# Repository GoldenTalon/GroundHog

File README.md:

# GroundHog
WPT inverter design with dynamic all off time and dynamic frequency.

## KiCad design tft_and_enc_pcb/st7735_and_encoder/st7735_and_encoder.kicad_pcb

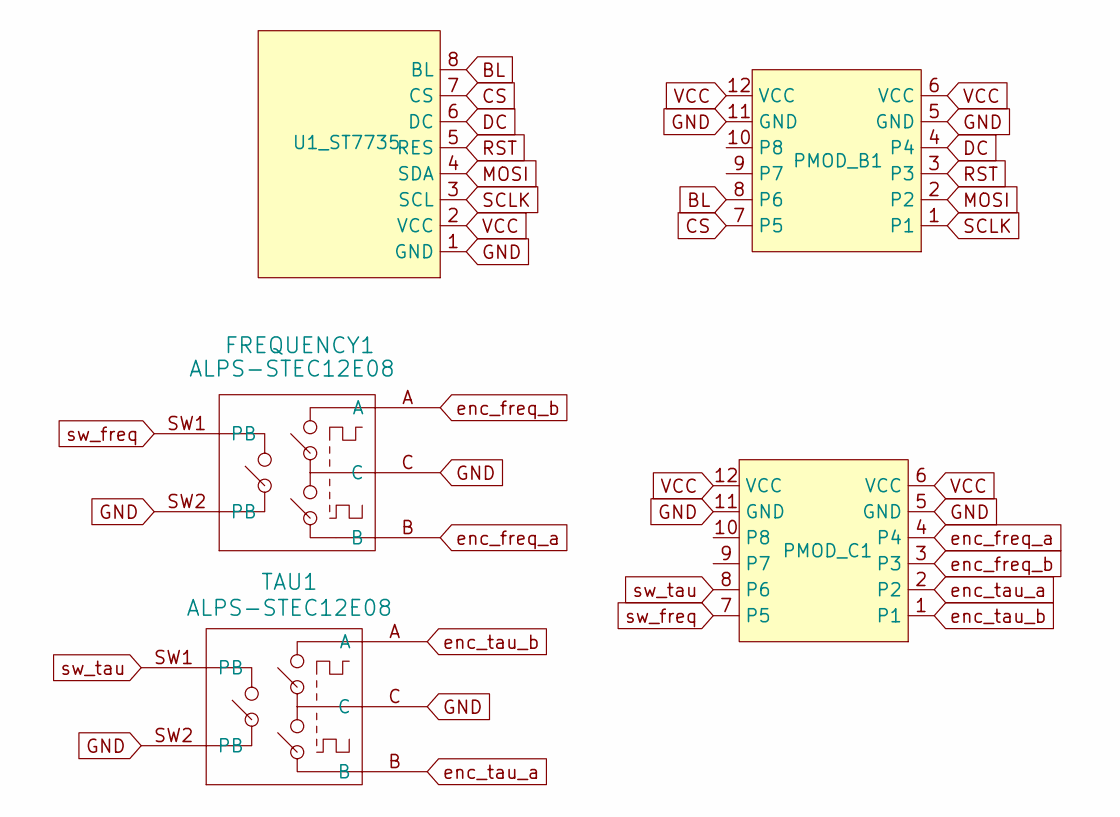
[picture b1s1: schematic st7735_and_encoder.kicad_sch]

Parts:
FREQUENCY1: ALPS-STEC12E08; ALPS_STEC12E08
PMOD_B1: pmod_end_launch
PMOD_C1: pmod_end_launch
TAU1: ALPS-STEC12E08; ALPS_STEC12E08
U1_ST7735: ST7735

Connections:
BL: PMOD_B1.8 (P6), U1_ST7735.8 (BL)
CS: PMOD_B1.7 (P5), U1_ST7735.7 (CS)
DC: PMOD_B1.4, U1_ST7735.6 (DC)
GND: FREQUENCY1.C, FREQUENCY1.SW2 (PB), PMOD_B1.5 (GND), PMOD_B1.11 (GND), PMOD_C1.5 (GND), PMOD_C1.11 (GND), TAU1.C, TAU1.SW2 (PB), U1_ST7735.1 (GND)
MOSI: PMOD_B1.2, U1_ST7735.4 (SDA)
RST: PMOD_B1.3, U1_ST7735.5 (RES)
SCLK: PMOD_B1.1, U1_ST7735.3 (SCL)
VCC: PMOD_B1.6 (VCC), PMOD_B1.12 (VCC), PMOD_C1.6 (VCC), PMOD_C1.12 (VCC), U1_ST7735.2 (VCC)
enc_freq_a: FREQUENCY1.B, PMOD_C1.4
enc_freq_b: FREQUENCY1.A, PMOD_C1.3
enc_tau_a: PMOD_C1.2, TAU1.B
enc_tau_b: PMOD_C1.1, TAU1.A
sw_freq: FREQUENCY1.SW1 (PB), PMOD_C1.7 (P5)
sw_tau: PMOD_C1.8 (P6), TAU1.SW1 (PB)

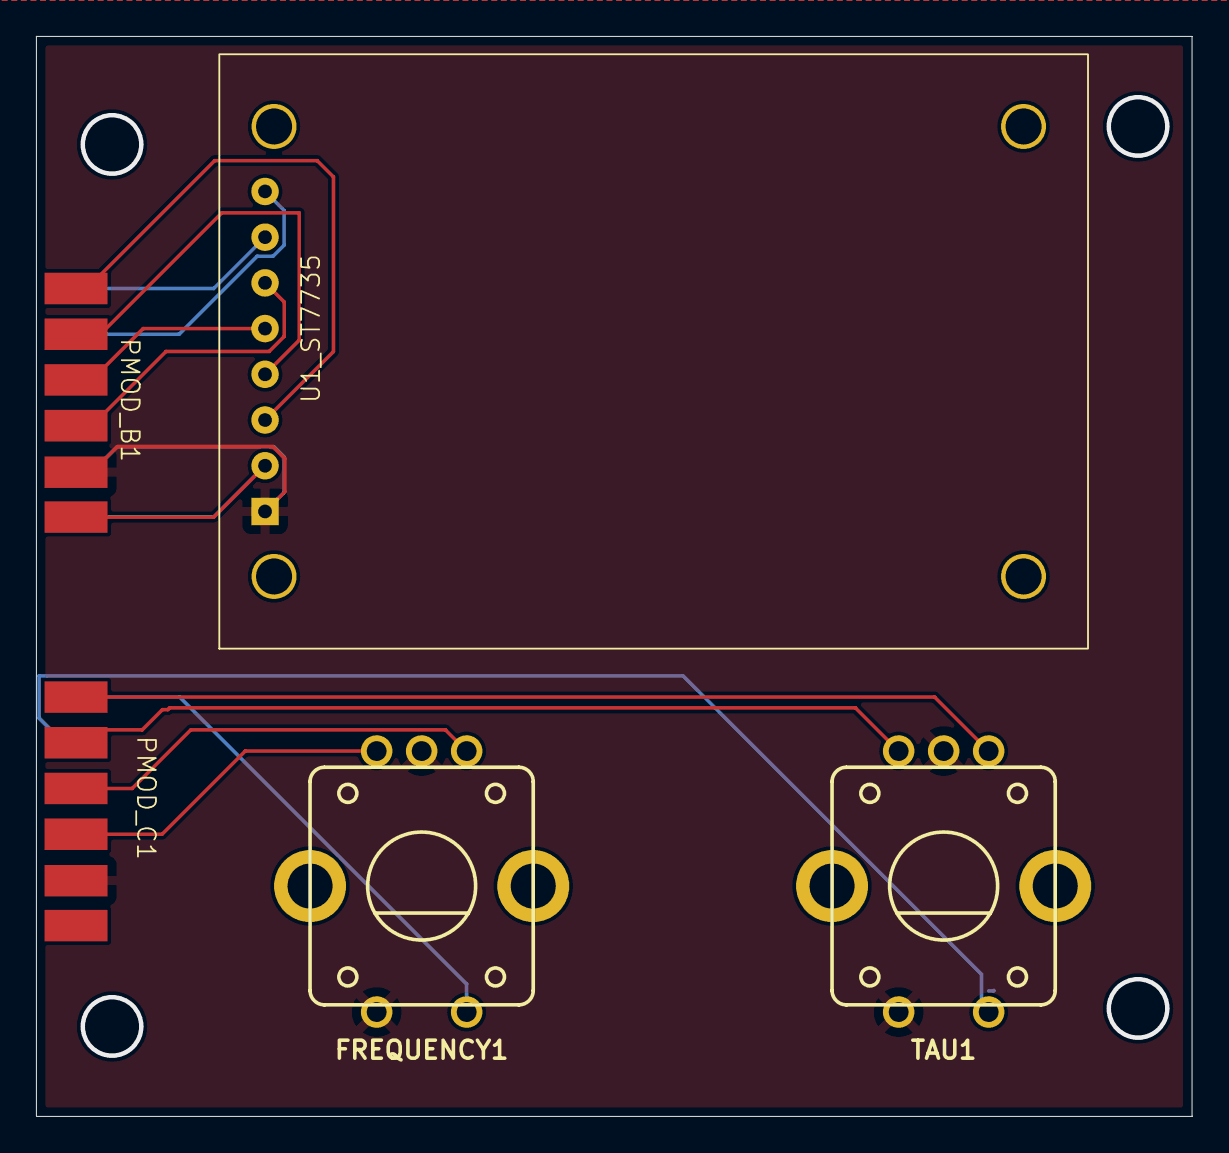
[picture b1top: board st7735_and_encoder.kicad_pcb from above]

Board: 2 copper layers, 64.2 x 60.0 mm, 5 parts (0 on the bottom side), 14 nets.

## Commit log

2024-09-17 Has a rotarty encoder error. Need better debouncing. Also, all the designs are dependent on RTL or drag-and-drop ip. Trying to be more formal in the simulation before implementation.
2024-09-21 Corrected state macheine IP. Added microblaze processor and vitis project.Next going to try and test flash memory for non-volitile changes.
2024-09-23 previous commits had a too strong of a git ignore. removing it.
2024-10-17 Variable frequency, however not all of the frequency resolution at 5 MHz or more. Possible timming issue. Also new dual encoder layout.
2024-10-25 Appears to be functioning correctly. Some Jutter but Clock up to 15 MHz.
